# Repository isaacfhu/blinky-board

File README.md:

# blinky-board
My first hardware project
A 555 LED chaser PCB project 
Building by following: https://stasis.hackclub.com/starter-projects/blinky

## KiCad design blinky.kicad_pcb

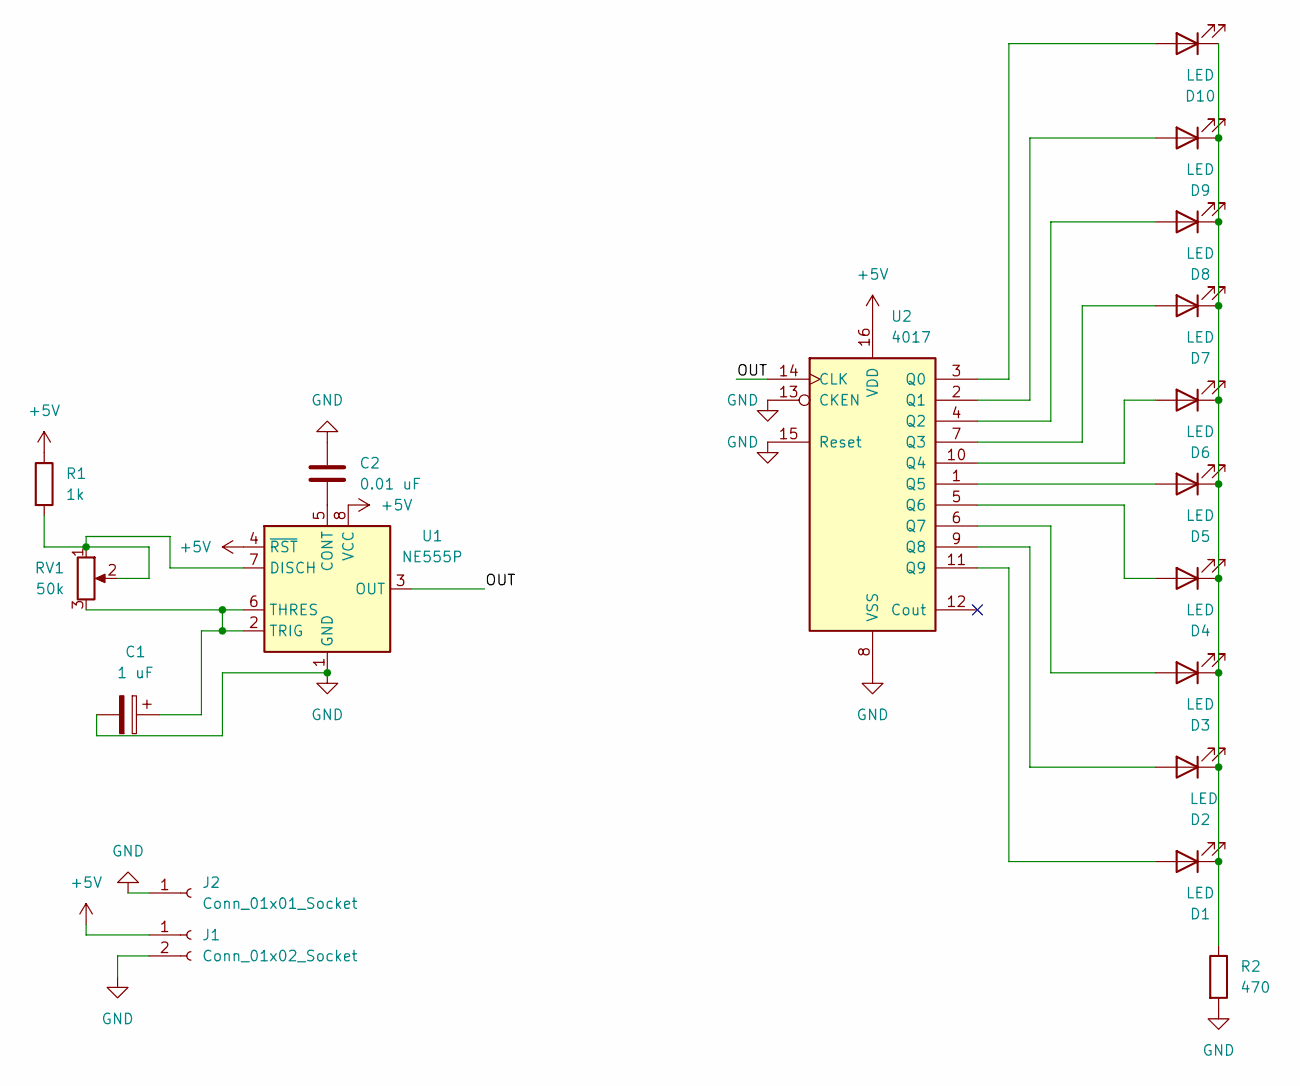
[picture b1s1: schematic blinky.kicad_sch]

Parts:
C1: 1 uF; CP_Radial_D5.0mm_P2.00mm
C2: 0.01 uF; C_Disc_D7.5mm_W2.5mm_P5.00mm
D1, D2, D3, D4, D5, D6, D7, D8, D9, D10: LED; LED_D3.0mm
J1: Conn_01x02_Socket; PinHeader_1x02_P2.54mm_Vertical
J2: Conn_01x01_Socket; PinHeader_1x01_P2.54mm_Vertical
R1: 1k; R_Axial_DIN0207_L6.3mm_D2.5mm_P7.62mm_Horizontal
R2: 470; R_Axial_DIN0207_L6.3mm_D2.5mm_P7.62mm_Horizontal
RV1: 50k; Potentiometer_Vishay_T93YA_Vertical
U1: NE555P; DIP-8_W7.62mm
U2: 4017; CD4017BE

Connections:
+5V: J1.1, R1.1, U1.4 (~RST), U1.8 (VCC), U2.16 (VDD)
/OUT: U1.3 (OUT), U2.14 (CLK)
GND: C1.2, C2.1, J1.2, J2.1 (Pin_1_1), R2.2, U1.1 (GND), U2.8 (VSS), U2.13 (CKEN), U2.15 (Reset)
unnamed: D1.2 (A), U2.11 (Q9)
unnamed: D1.1 (K), D2.1 (K), D3.1 (K), D4.1 (K), D5.1 (K), D6.1 (K), D7.1 (K), D8.1 (K), D9.1 (K), D10.1 (K), R2.1
unnamed: D2.2 (A), U2.9 (Q8)
unnamed: D3.2 (A), U2.6 (Q7)
unnamed: D4.2 (A), U2.5 (Q6)
unnamed: D5.2 (A), U2.1 (Q5)
unnamed: D6.2 (A), U2.10 (Q4)
unnamed: D7.2 (A), U2.7 (Q3)
unnamed: D8.2 (A), U2.4 (Q2)
unnamed: D9.2 (A), U2.2 (Q1)
unnamed: D10.2 (A), U2.3 (Q0)
unnamed: C2.2, U1.5 (CONT)
unnamed: R1.2, RV1.1, RV1.2, U1.7 (DISCH)
unnamed: C1.1, RV1.3, U1.2 (TRIG), U1.6 (THRES)

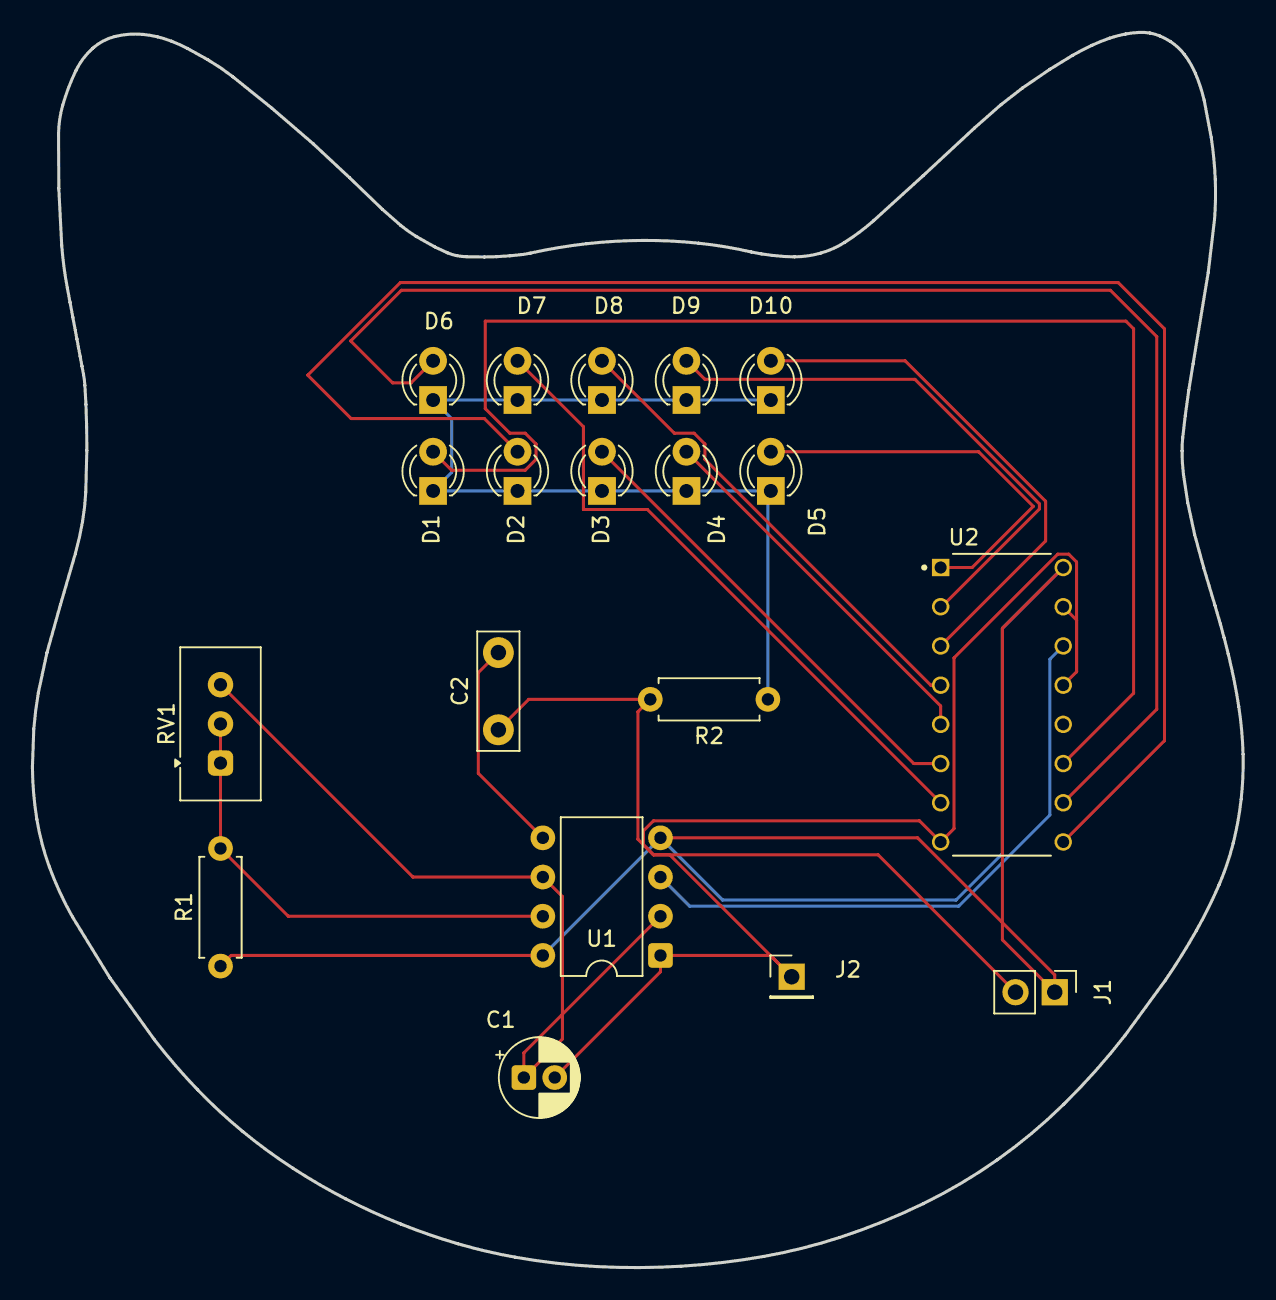
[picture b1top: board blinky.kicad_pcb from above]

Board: 2 copper layers, 78.4 x 80.0 mm, 19 parts (0 on the bottom side), 17 nets.

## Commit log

2026-05-18 Add project description and reference link
2026-05-20 Include image in README for blinky-board project
    Add project image to README
2026-05-20 Upload of files
2026-05-20 Upload of files 2
2026-05-20 Upload Gerbers files
2026-05-20 Added screenshot
